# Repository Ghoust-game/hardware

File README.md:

# GHOUST HARDWARE

This repository is all about the **HARDWARE** used in the **GHOUST** game

You find eagle (v6) files in here
- .sch Schematics
- .brd Board layout files
- .pdf files of the Schematics 
- Bill of Materials
- Links to all Parts

Also GERBER files are provided if you want to make your own Boards

If you expect / need something that is not here, please let us know via email: team@ghou.st

Information on sourcing the parts is available on the [wiki](https://github.com/Ghoust-game/hardware/wiki).

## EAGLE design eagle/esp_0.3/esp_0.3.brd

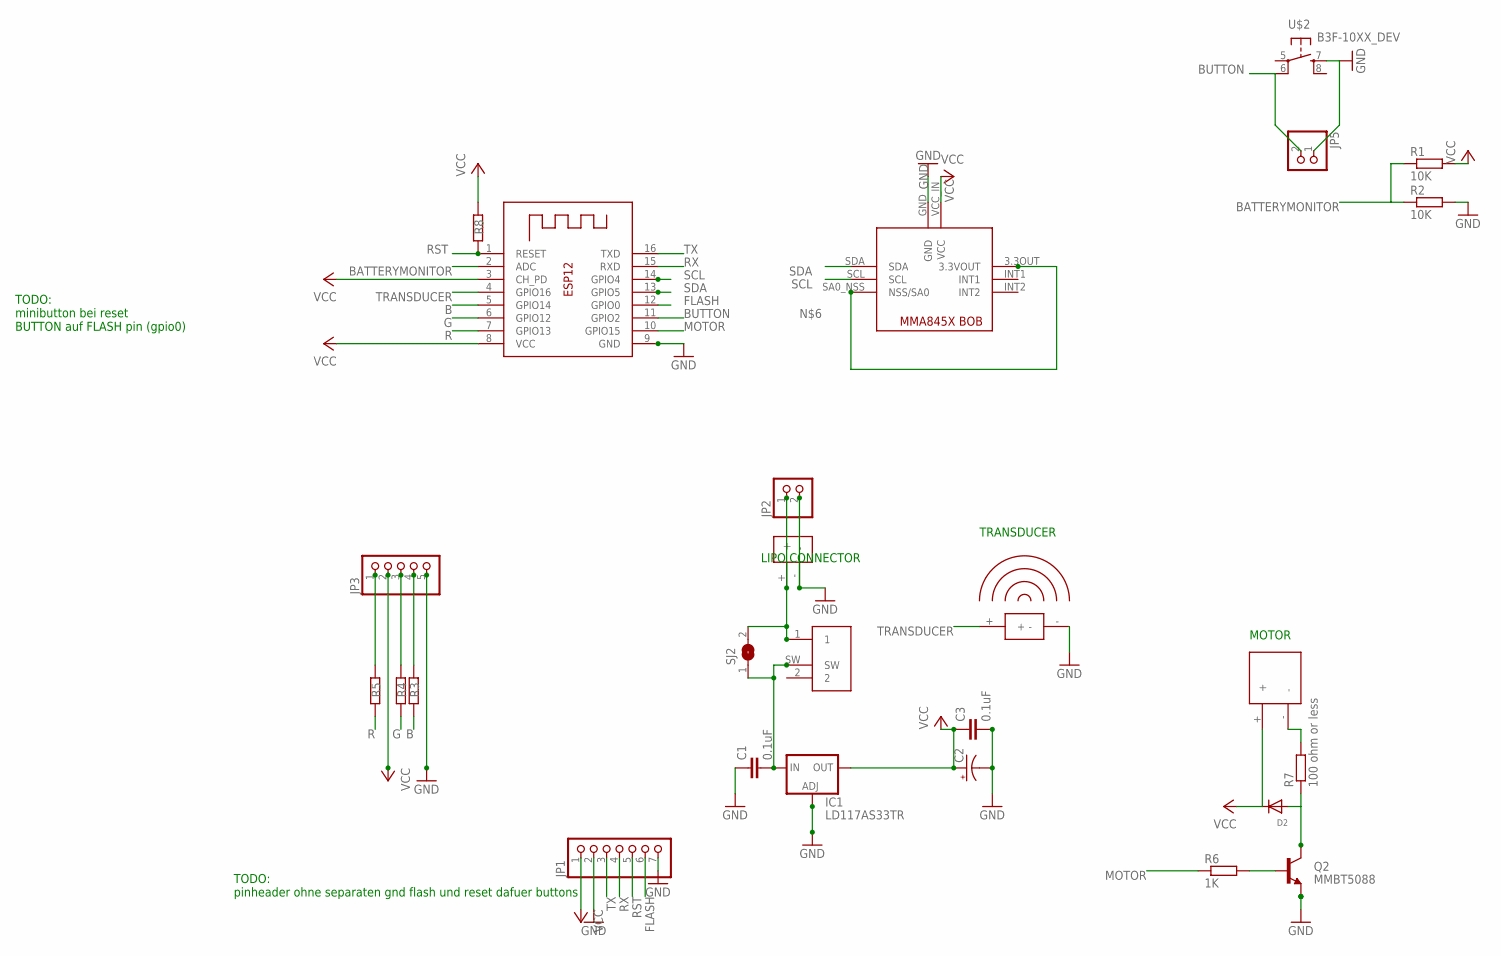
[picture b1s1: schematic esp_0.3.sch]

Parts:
C1, C3: 0.1uF; 0805
C2: 100UF-25V-20%(PTH); CPOL-RADIAL-100UF-25V
D2: DIODE_SOD-123FL; SOD-123FL
IC1: LD117AS33TR; SOT223
JP1: PINHD-1X7; 1X07
JP2: PINHD-1X2; 1X02
JP3: PINHD-1X5; 1X05
JP5: PINHD-1X2/90; 1X02/90
Q2: MMBT5088; SOT23-3
R1, R2: 10K; R0805
R3, R4, R5, R6: 1K; R0805
R7: 100 ohm or less; R0805
R8: 56K pullup; R0805
SJ2: SJ
U$1: MMA845X_BREAKOUT; MMA845XBOB
U$2: B3F-10XX_DEV; B3F-10XX
U$8: TRANSDUCER; BMT1205XH7.5
U$11: MICROSWITCH; MICR_SCHIEBESCHALTER_CHINA_PAC
U$12: VIBROMOTOR; VIBRO
U$13: LIPO; LIPOCON
X2: ESP-12

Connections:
B: R3.1, X2.5 (GPIO14)
BATTERYMONITOR: R1.1, R2.1, X2.2 (ADC)
BUTTON: JP5.2, U$2.6 (P1), X2.11 (GPIO2)
FLASH: JP1.6, X2.12 (GPIO0)
G: R4.1, X2.6 (GPIO12)
GND: C1.1, C2.2 (-), C3.2, IC1.1 (ADJ), JP1.2, JP1.7, JP2.2, JP3.5, JP5.1, Q2.2 (E), R2.2, U$1.GND, U$2.7 (S), U$8.-, U$13.-, X2.9 (GND)
MOTOR: R6.1, X2.10 (GPIO15)
unnamed: R7.2, U$12.-
unnamed: JP2.1, SJ2.2, U$11.1, U$13.+
unnamed: D2.A, Q2.3 (C), R7.1
unnamed: Q2.1 (B), R6.2
unnamed: C1.2, IC1.3 (IN), SJ2.1, U$11.SW
unnamed: U$1.3.3OUT (3.3VOUT), U$1.SA0_NSS (NSS/SA0)
R: R5.1, X2.7 (GPIO13)
RST: JP1.5, R8.1, X2.1 (RESET)
RX: JP1.4, X2.15 (RXD)
SCL: U$1.SCL, X2.14 (GPIO4)
SDA: U$1.SDA, X2.13 (GPIO5)
TRANSDUCER: U$8.+, X2.4 (GPIO16)
TX: JP1.3, X2.16 (TXD)
VCC: C2.1 (+), C3.1, D2.C, IC1.4 (OUT), JP1.1, JP3.2, R1.2, R8.2, U$1.VCC_IN (VCC), U$12.+, X2.3 (CH_PD), X2.8 (VCC)
XX: JP3.1, R5.2
XXX: JP3.3, R4.2
XXXX: JP3.4, R3.2

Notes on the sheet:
MOTOR
LIPO CONNECTOR
TRANSDUCER
TODO: minibutton bei reset BUTTON auf FLASH pin (gpio0)
TODO: pinheader ohne separaten gnd flash und reset dafuer buttons

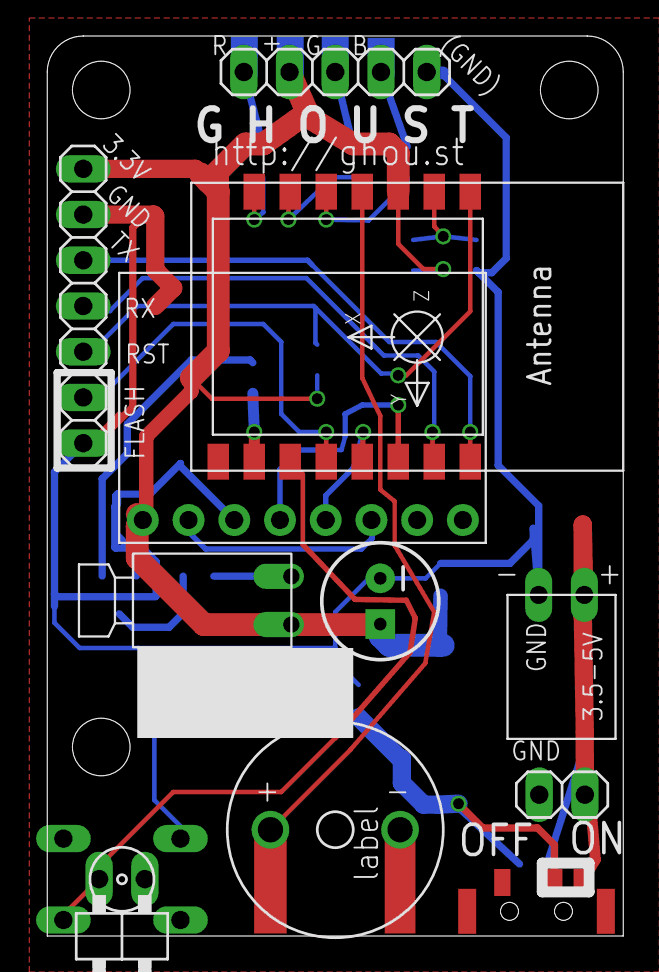
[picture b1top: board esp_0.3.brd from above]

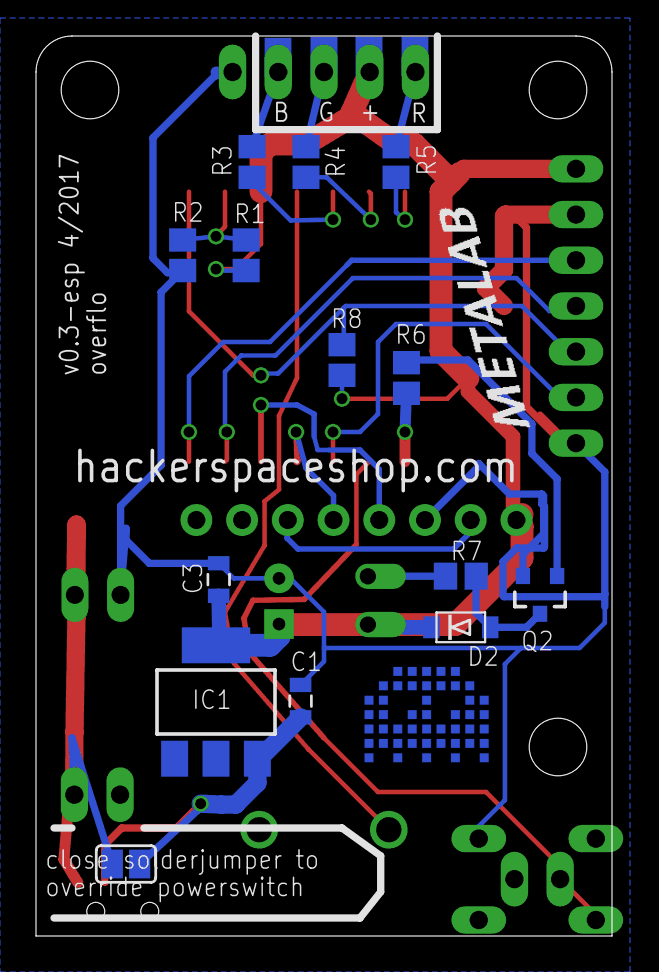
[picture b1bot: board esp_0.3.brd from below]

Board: 2 copper layers, 32.0 x 50.0 mm, 28 parts (16 on the bottom side), 24 nets.

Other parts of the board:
U$4: METALAB
U$6: GHOUT_LOGO; GHOUST_LOGO

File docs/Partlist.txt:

Part     Value            Package                     Link    

C1       0.1uF            0805                        http://mouser.com    
C2                        CPOL-RADIAL-100UF-25V       http://mouser.com   
C3       0.1uF            0805                        http://mouser.com   

D2                        SOD-123FL                   http://mouser.com   

Q2       MMBT5088         SOT23-3                     http://mouser.com   

R1       10K              R0805                       http://mouser.com    
R2       10K              R0805                       http://mouser.com   
R3       1K               R0805                       http://mouser.com   
R4       1K               R0805                       http://mouser.com   
R5       1K               R0805                       http://mouser.com   
R6       1K               R0805                       http://mouser.com   
R7       100ohm 	  R0805                       http://mouser.com   
R8       56K pullup       R0805                       http://mouser.com   


IC1      AMS1117          SOT223                      http://www.electrodragon.com/product/10pcs-ams1117-lm1117-11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

U$1      MMA845X_BREAKOUT MMA845XBOB                  http://www.electrodragon.com/product/triple-axis-acceleromet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    
U$2      B3F-10XX_DEV     B3F-10XX                    http://www.electrodragon.com/product/mini-push-button-switch/
U$8      TRANSDUCER       BMT1205XH7.5                https://www.reichelt.at/Alarmmelder/SUMMER-EPM-121/3/index.h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      
U$11     MICROSWITCH       			      https://www.aliexpress.com/item/6-7-2-7-1-5-3pin-slide-switc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
U$12     VIBROMOTOR       VIBRO                       https://de.aliexpress.com/item/3-Pcs-1400RPM-Speed-3V-Mobile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    
U$13     LIPO             LIPOCON                     https://www.aliexpress.com/item/100pcs-XH-2-5-2-54mm-2P-3P-4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
X2                        ESP-12                      http://www.electrodragon.com/product/esp-12s-wifi-module-esp8266/

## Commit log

2017-04-25 'ello!
2017-04-25 docs
2017-04-25 eagle(6.4) files

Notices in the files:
parts and their libraries:
SparkFun-DiscreteSemi: Licensing: Creative Commons ShareAlike 4.0 International - https://creativecommons.org/licenses/by-sa/4.0
